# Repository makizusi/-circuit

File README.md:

https://github.com/makizusi/-circuit/blob/main/%E8%A8%AD%E8%A8%88%E6%84%8F%E5%9B%B3.pdf

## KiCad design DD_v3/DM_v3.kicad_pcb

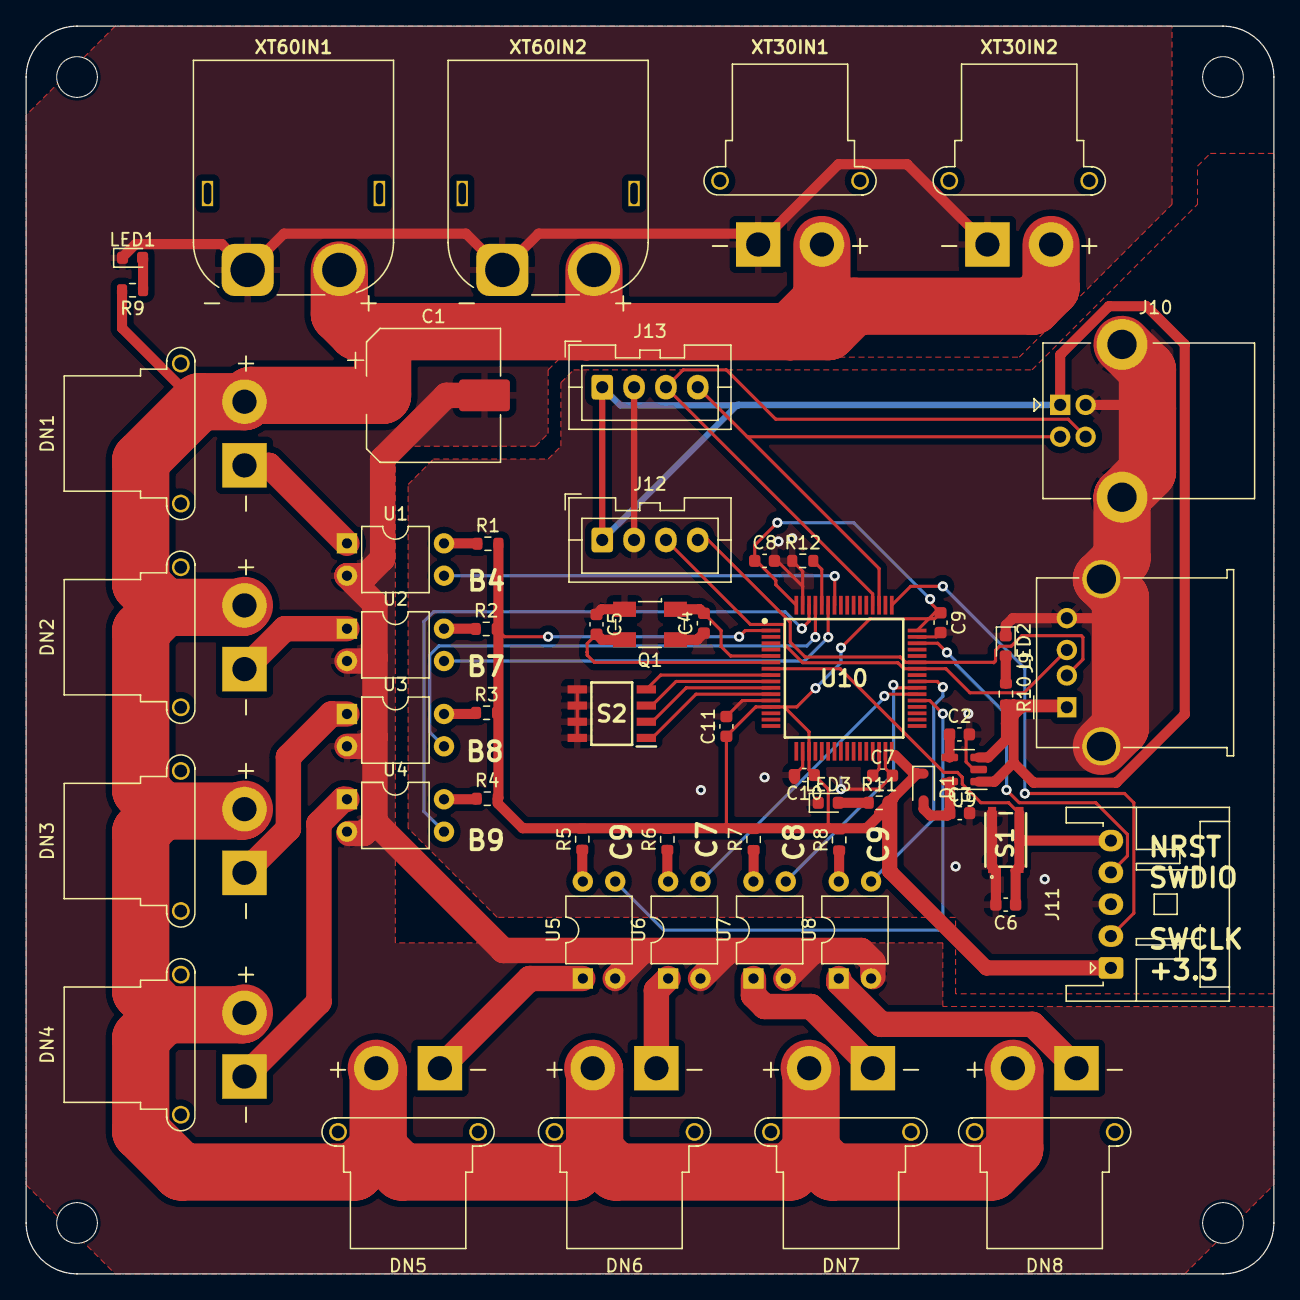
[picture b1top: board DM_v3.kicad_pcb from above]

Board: 2 copper layers, 98.0 x 98.0 mm, 57 parts (0 on the bottom side), 49 nets.

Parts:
C1: 330μf; CP_Elec_10x10
C2: 4.7nF; C_0603_1608Metric
C3: 2.2uF; C_0603_1608Metric
C4, C5: 22pF; C_0603_1608Metric
C6, C8, C9, C10, C11: 0.1uF; C_0603_1608Metric
C7: 4.7uF; C_0603_1608Metric
D1: BAT60JFILM; D_SOD-323
DN1, DN2, DN3, DN4, DN5, DN6, DN7, DN8: Conn_01x02; AMASS_XT30PW-F_1x02_P2.50mm_Horizontal
J9: USB_A; USB_A_Molex_67643_Horizontal
J10: USB_B; USB_B_Lumberg_2411_02_Horizontal
J11: stlink; JST_XA_S05B-XASK-1_1x05_P2.50mm_Horizontal
J12, J13: Conn_01x04; JST_XA_B04B-XASK-1_1x04_P2.50mm_Vertical
LED1: vcc; LED_0603_1608Metric
LED2: 5v; LED_0603_1608Metric
LED3: 3.3v; LED_0603_1608Metric
Q1: ABM3B-8.000MHZ-B2-T; Crystal_SMD_Abracon_ABM3B-4Pin_5.0x3.2mm
R1, R2, R3, R4, R5, R6, R7, R8: 100; R_0603_1608Metric
R9, R10: 4.7k; R_0603_1608Metric
R11: 1k; R_0603_1608Metric
R12: 10k; R_0603_1608Metric
S1: SKRPACE010; SMT_4.2X3.2_
S2: KHS42E; NE555DR
U1, U2, U3, U4, U5, U6, U7, U8: TLP627; DIP-4_W7.62mm
U9: SPX3819M5-L; SOT-23-5
U10: STM32F446RCT7; QFP50P1200X1200X160-64N
XT30IN1, XT30IN2: Conn_01x02; AMASS_XT30PW-F_1x02_P2.50mm_Horizontal
XT60IN1, XT60IN2: power; AMASS_XT60PW-M_1x02_P7.20mm_Horizontal

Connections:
+3.3V: C8.1, C9.1, C10.1, C11.1, D1.1, J11.1, R1.2, R2.2, R3.2, R4.2, R5.2, R6.2, R7.2, R8.2, R11.2, U10.1 (VBAT), U10.13 (VDDA/VREF+), U10.19 (VDD_4), U10.32 (VDD_1), U10.48 (VDD_2), U10.64 (VDD_3)
+5V: J9.1 (VBUS), J10.1 (VBUS), J12.1, J13.1, R10.2, U9.1 (IN), U9.3 (EN)
A9: J9.3 (D+), J12.3, U10.42 (PA9)
A10: J9.2 (D-), J12.4, U10.43 (PA10)
B6: U1.3, U10.58 (PB6)
B7: U2.3, U10.59 (PB7)
B8: U3.3, U10.61 (PB8)
B9: U4.3, U10.62 (PB9)
C6: U5.3, U10.37 (PC6)
C7: U6.3, U10.38 (PC7)
C8: U7.3, U10.39 (PC8)
C9: U8.3, U10.40 (PC9)
C10: J10.2 (D-), J13.4, U10.51 (PC10)
C11: J10.3 (D+), J13.3, U10.52 (PC11)
GND: C2.2, C3.2, C4.1, C5.1, C6.2, C7.2, C8.2, C9.2, C10.2, C11.2, J9.4 (GND), J9.5 (Shield), J10.4 (GND), J10.5 (Shield), J11.3, J12.2, J13.2, LED2.1 (K), LED3.1 (K), Q1.2 (GND), Q1.4 (GND), R12.1, S1.1, S1.2, S2.5, S2.6, S2.7, S2.8, U9.2 (GND), U10.12 (VSSA/VREF-), U10.18 (VSS_4), U10.31 (VSS_1), U10.47 (VSS_2), U10.63 (VSS_3)
GNDPWR: C1.2, LED1.1 (K), U1.2, U2.2, U3.2, U4.2, U5.2, U6.2, U7.2, U8.2, XT30IN1.1, XT30IN2.1, XT60IN1.1, XT60IN2.1
unnamed: DN1.1, U1.1
unnamed: DN2.1, U2.1
unnamed: DN3.1, U3.1
unnamed: DN4.1, U4.1
unnamed: DN5.1, U5.1
unnamed: DN6.1, U6.1
unnamed: DN7.1, U7.1
unnamed: DN8.1, U8.1
unnamed: LED1.2 (A), R9.1
unnamed: LED2.2 (A), R10.1
unnamed: LED3.2 (A), R11.1
unnamed: R1.1, U1.4
unnamed: R2.1, U2.4
unnamed: R3.1, U3.4
unnamed: R4.1, U4.4
unnamed: R5.1, U5.4
unnamed: R6.1, U6.4
unnamed: R7.1, U7.4
unnamed: R8.1, U8.4
unnamed: C2.1, U9.4 (ADJ)
unnamed: C3.1, D1.2, U9.5 (OUT)
unnamed: R12.2, U10.60 (BOOT0)
unnamed: S2.4, U10.8 (PC0)
unnamed: S2.3, U10.9 (PC1)
unnamed: S2.2, U10.10 (PC2)
unnamed: S2.1, U10.11 (PC3)
unnamed: C4.2, Q1.1, U10.5 (PH0-OSC_IN)
unnamed: C5.2, Q1.3, U10.6 (PH1-OSC_OUT)
unnamed: C7.1, U10.30 (VCAP_1)
VCC: C1.1, DN1.2, DN2.2, DN3.2, DN4.2, DN5.2, DN6.2, DN7.2, DN8.2, R9.2, XT30IN1.2, XT30IN2.2, XT60IN1.2, XT60IN2.2
nrst: C6.1, J11.5, S1.3, S1.4, U10.7 (NRST)
swclk: J11.2, U10.49 (PA14)
swdio: J11.4, U10.46 (PA13)

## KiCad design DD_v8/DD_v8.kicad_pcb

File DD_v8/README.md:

# ALTAIR_SERVO_MODULE_V6
ALTAIR_SERVO_MODULE_V6

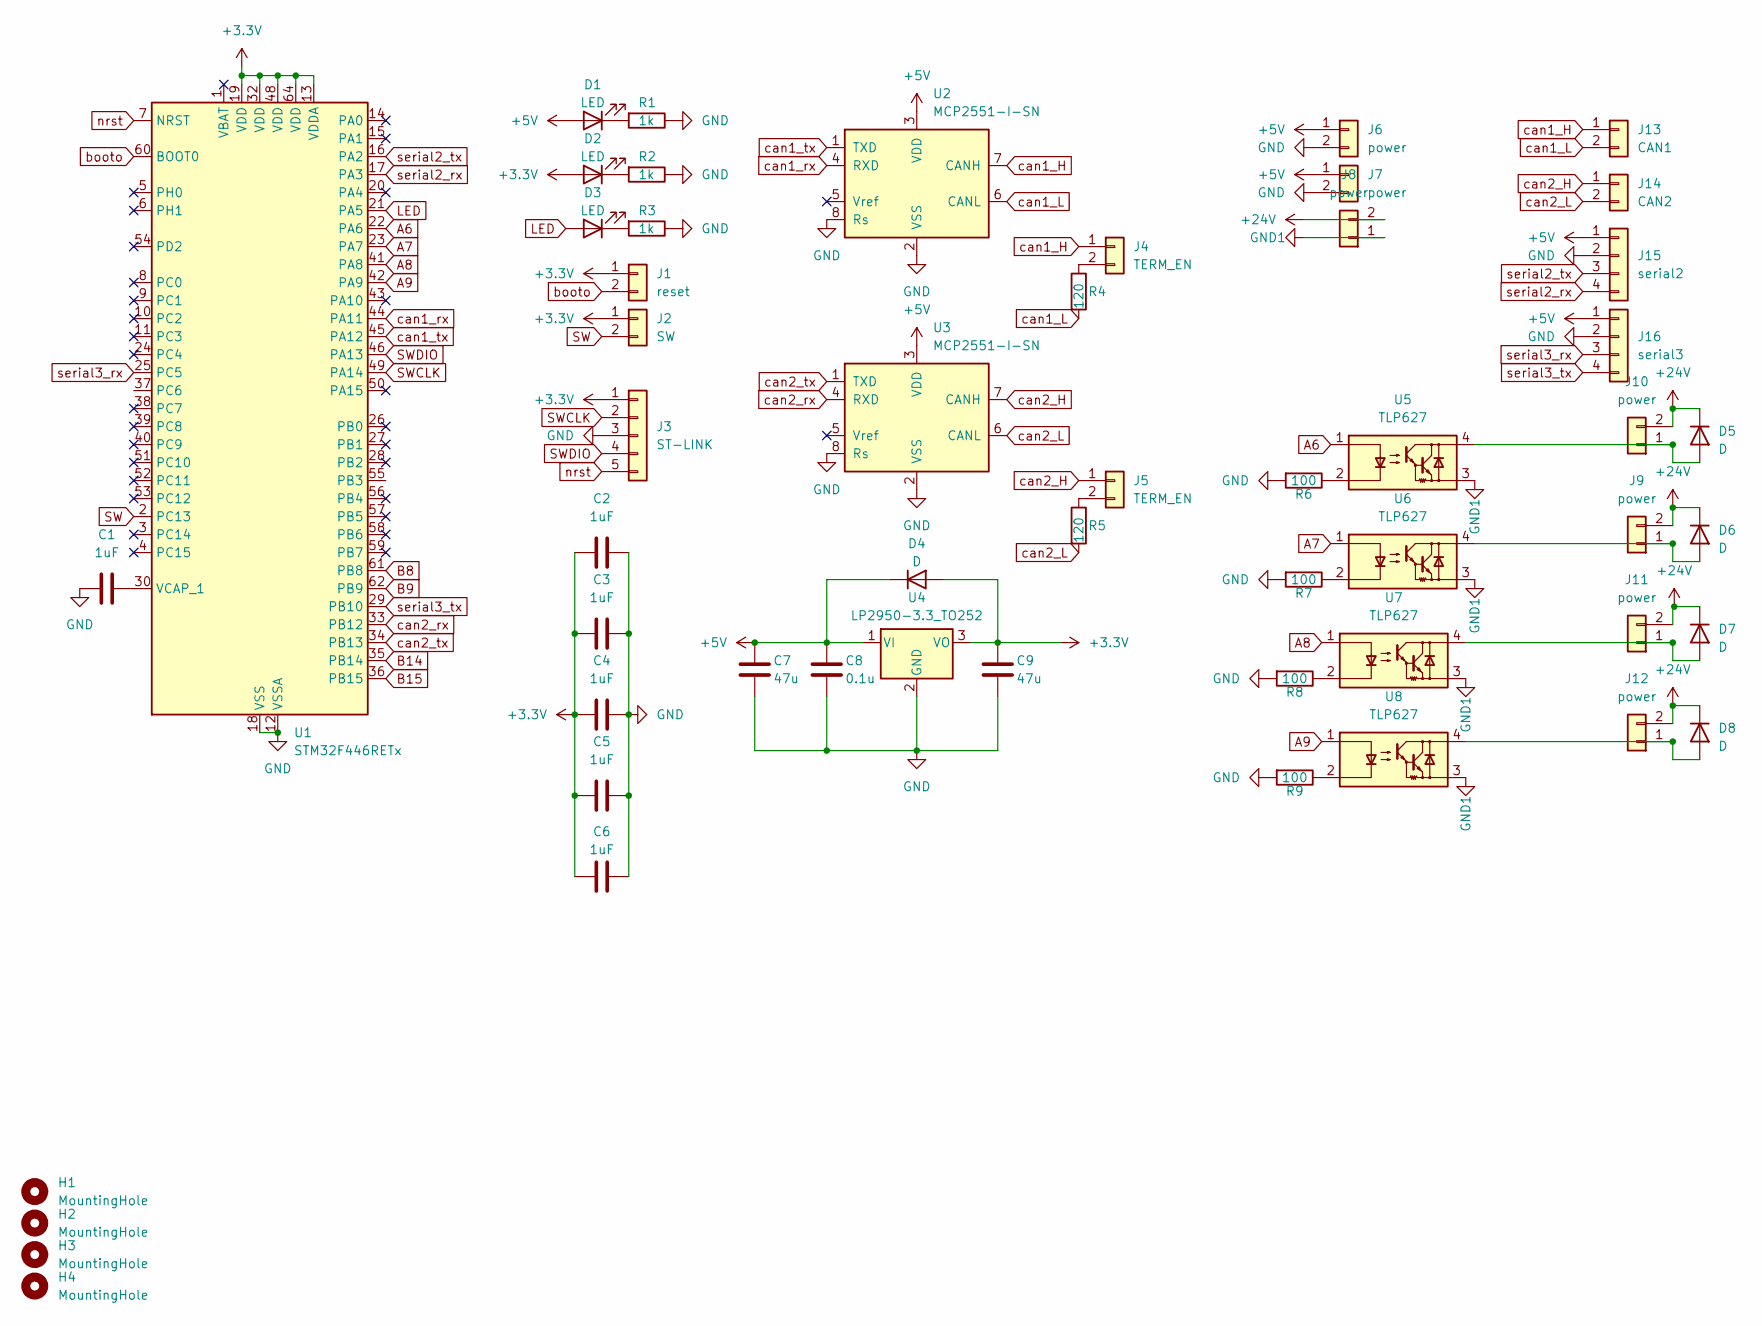
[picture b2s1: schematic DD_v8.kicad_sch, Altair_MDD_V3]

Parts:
C1, C2, C3, C4, C5, C6: 1uF; C_0603_1608Metric
C7, C9: 47u; C_0603_1608Metric
C8: 0.1u; C_0603_1608Metric
D1, D2, D3: LED; LED_0603_1608Metric
D4: D; D_0603_1608Metric
D5, D6, D7, D8: D; D_SOD-128
H1, H2, H3, H4: MountingHole; MountingHole_3.2mm_M3_Pad_Via
J1: reset; PinSocket_1x02_P2.54mm_Vertical
J2: SW; PinSocket_1x02_P2.54mm_Vertical
J3: ST-LINK; PinSocket_1x05_P2.54mm_Vertical
J4, J5: TERM_EN; PinSocket_1x02_P2.54mm_Vertical
J6, J7: power; JST_XA_S02B-XASK-1_1x02_P2.50mm_Horizontal
J8, J9, J10, J11, J12: power; AMASS_XT30PW-M_1x02_P2.50mm_Horizontal
J13: CAN1; JST_XA_S02B-XASK-1_1x02_P2.50mm_Horizontal
J14: CAN2; JST_XA_S02B-XASK-1_1x02_P2.50mm_Horizontal
J15: serial2; JST_XA_B04B-XASK-1-A_1x04_P2.50mm_Vertical
J16: serial3; JST_XA_B04B-XASK-1-A_1x04_P2.50mm_Vertical
R1, R2, R3: 1k; R_0603_1608Metric
R4, R5: 120; R_0603_1608Metric
R6, R7, R8, R9: 100; R_0603_1608Metric
U1: STM32F446RETx; LQFP-64_10x10mm_P0.5mm
U2, U3: MCP2551-I-SN; SOIC-8_3.9x4.9mm_P1.27mm
U4: LP2950-3.3_TO252; TO-252-2
U5, U6, U7, U8: TLP627; DIP-4_W7.62mm_SMDSocket_SmallPads

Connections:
+3.3V: C2.1, C3.1, C4.1, C5.1, C6.1, C9.1, D2.2 (A), D4.2 (A), J1.1, J2.1, J3.1, U1.13 (VDDA), U1.19 (VDD), U1.32 (VDD), U1.48 (VDD), U1.64 (VDD), U4.3 (VO)
+5V: C7.1, C8.1, D1.2 (A), D4.1 (K), J6.1, J7.1, J15.1, J16.1, U2.3 (VDD), U3.3 (VDD), U4.1 (VI)
+24V: D5.1 (K), D6.1 (K), D7.1 (K), D8.1 (K), J8.2, J9.2, J10.2, J11.2, J12.2
A6: U1.22 (PA6), U5.1
A7: U1.23 (PA7), U6.1
A8: U1.41 (PA8), U7.1
A9: U1.42 (PA9), U8.1
B8: U1.61 (PB8)
B9: U1.62 (PB9)
B14: U1.35 (PB14)
B15: U1.36 (PB15)
GND: C1.1, C2.2, C3.2, C4.2, C5.2, C6.2, C7.2, C8.2, C9.2, J3.3, J6.2, J7.2, J15.2, J16.2, R1.1, R2.1, R3.1, R6.2, R7.2, R8.2, R9.2, U1.12 (VSSA), U1.18 (VSS), U1.31 (VSS), U1.47 (VSS), U1.63 (VSS), U2.2 (VSS), U2.8 (Rs), U3.2 (VSS), U3.8 (Rs), U4.2 (GND)
GND1: J8.1, U5.3, U6.3, U7.3, U8.3
LED: D3.2 (A), U1.21 (PA5)
unnamed: D1.1 (K), R1.2
unnamed: D2.1 (K), R2.2
unnamed: D3.1 (K), R3.2
unnamed: D5.2 (A), J10.1, U5.4
unnamed: D6.2 (A), J9.1, U6.4
unnamed: D7.2 (A), J11.1, U7.4
unnamed: D8.2 (A), J12.1, U8.4
unnamed: J4.2, R4.1
unnamed: J5.2, R5.1
unnamed: R6.1, U5.2
unnamed: R7.1, U6.2
unnamed: R8.1, U7.2
unnamed: R9.1, U8.2
unnamed: C1.2, U1.30 (VCAP_1)
SW: J2.2, U1.2 (PC13)
SWCLK: J3.2, U1.49 (PA14)
SWDIO: J3.4, U1.46 (PA13)
booto: J1.2, U1.60 (BOOT0)
can1_H: J4.1, J13.1, U2.7 (CANH)
can1_L: J13.2, R4.2, U2.6 (CANL)
can1_rx: U1.44 (PA11), U2.4 (RXD)
can1_tx: U1.45 (PA12), U2.1 (TXD)
can2_H: J5.1, J14.1, U3.7 (CANH)
can2_L: J14.2, R5.2, U3.6 (CANL)
can2_rx: U1.33 (PB12), U3.4 (RXD)
can2_tx: U1.34 (PB13), U3.1 (TXD)
nrst: J3.5, U1.7 (NRST)
serial2_rx: J15.4, U1.17 (PA3)
serial2_tx: J15.3, U1.16 (PA2)
serial3_rx: J16.3, U1.25 (PC5)
serial3_tx: J16.4, U1.29 (PB10)

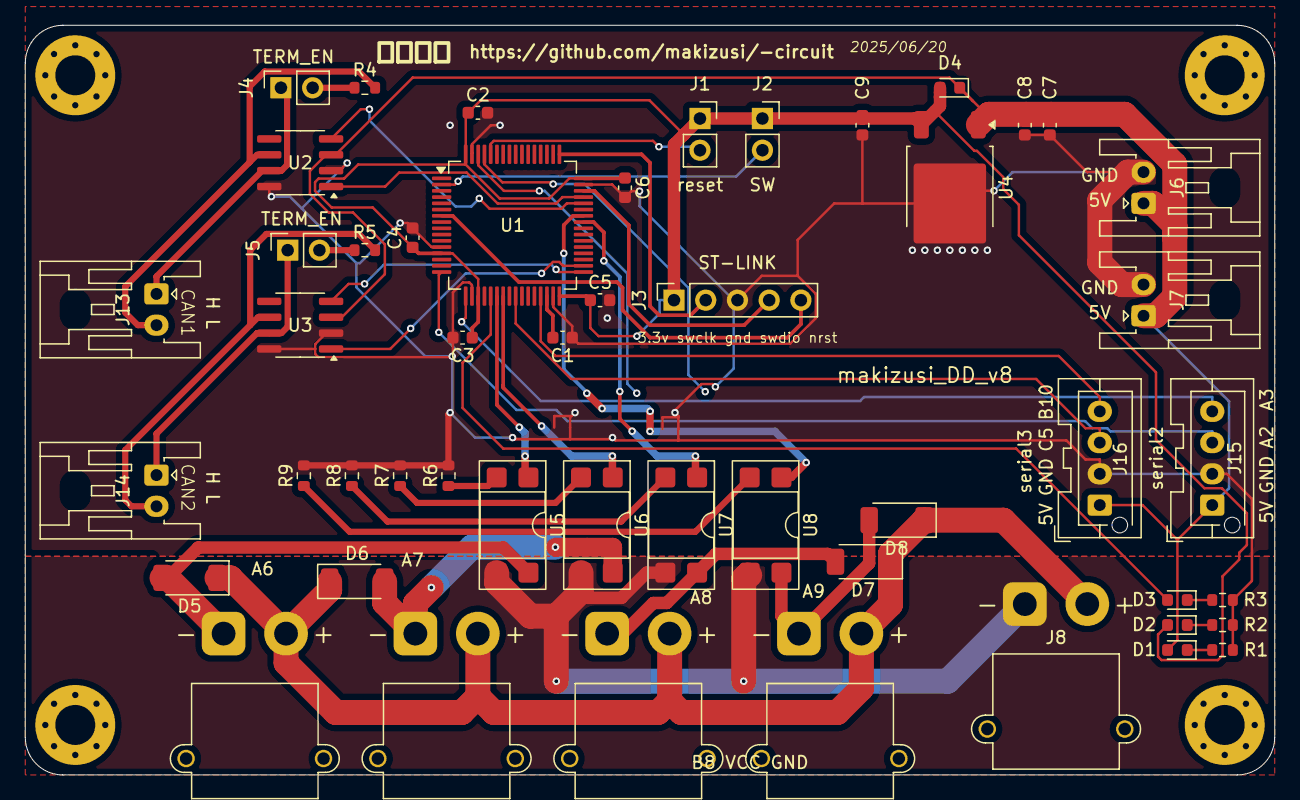
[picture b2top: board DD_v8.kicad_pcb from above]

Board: 2 copper layers, 100.0 x 60.0 mm, 54 parts (0 on the bottom side), 41 nets.

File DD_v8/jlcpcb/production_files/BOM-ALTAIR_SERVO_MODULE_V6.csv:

Comment,Designator,Footprint,LCSC,Quantity
0.1u,"C10,C12,C13,C8",C_0603_1608Metric,C125205,4
LP2950-3.3_TO252,U4,TO-252-2,C129994,1
47u,"C7,C9",C_0603_1608Metric,C140782,2
120,"R4,R5",R_0603_1608Metric,C14709,2
1uF,"C1,C2,C3,C4,C5,C6",C_0603_1608Metric,C1592,6
LED,"D1,D2,D3",LED_0603_1608Metric,C2290,3
TLP2105_F_,"IC1,IC2,IC3",TLP2105,C2880451,3
D,D4,D_0603_1608Metric,C3758192,1
STM32F446RETx,U1,LQFP-64_10x10mm_P0.5mm,C69336,1
MCP2551-I-SN,"U2,U3",SOIC-8_3.9x4.9mm_P1.27mm,C7376,2
1k,"R1,R2,R3",R_0603_1608Metric,C78748,3
Motor_Servo,M1,JST_XA_S03B-XASK-1_1x03_P2.50mm_Horizontal,,1
SW,J2,PinSocket_1x02_P2.54mm_Vertical,,1
power,J6,JST_XA_S02B-XASK-1_1x02_P2.50mm_Horizontal,,1
MountingHole,H2,MountingHole_3.2mm_M3_Pad_Via,,1
serial2,J15,JST_XA_B04B-XASK-1-A_1x04_P2.50mm_Vertical,,1
Motor_Servo,M5,JST_XA_S03B-XASK-1_1x03_P2.50mm_Horizontal,,1
TERM_EN,J4,PinSocket_1x02_P2.54mm_Vertical,,1
power,J8,AMASS_XT30PW-M_1x02_P2.50mm_Horizontal,,1
Motor_Servo,M2,JST_XA_S03B-XASK-1_1x03_P2.50mm_Horizontal,,1
serial3,J16,JST_XA_B04B-XASK-1-A_1x04_P2.50mm_Vertical,,1
reset,J1,PinSocket_1x02_P2.54mm_Vertical,,1
MountingHole,H1,MountingHole_3.2mm_M3_Pad_Via,,1
TERM_EN,J5,PinSocket_1x02_P2.54mm_Vertical,,1
Motor_Servo,M4,JST_XA_S03B-XASK-1_1x03_P2.50mm_Horizontal,,1
MountingHole,H4,MountingHole_3.2mm_M3_Pad_Via,,1
CAN2,J14,JST_XA_S02B-XASK-1_1x02_P2.50mm_Horizontal,,1
Motor_Servo,M3,JST_XA_S03B-XASK-1_1x03_P2.50mm_Horizontal,,1
ST-LINK,J3,PinSocket_1x05_P2.54mm_Vertical,,1
CAN1,J13,JST_XA_S02B-XASK-1_1x02_P2.50mm_Horizontal,,1
Motor_Servo,M6,JST_XA_S03B-XASK-1_1x03_P2.50mm_Horizontal,,1
power,J7,JST_XA_S02B-XASK-1_1x02_P2.50mm_Horizontal,,1
MountingHole,H3,MountingHole_3.2mm_M3_Pad_Via,,1

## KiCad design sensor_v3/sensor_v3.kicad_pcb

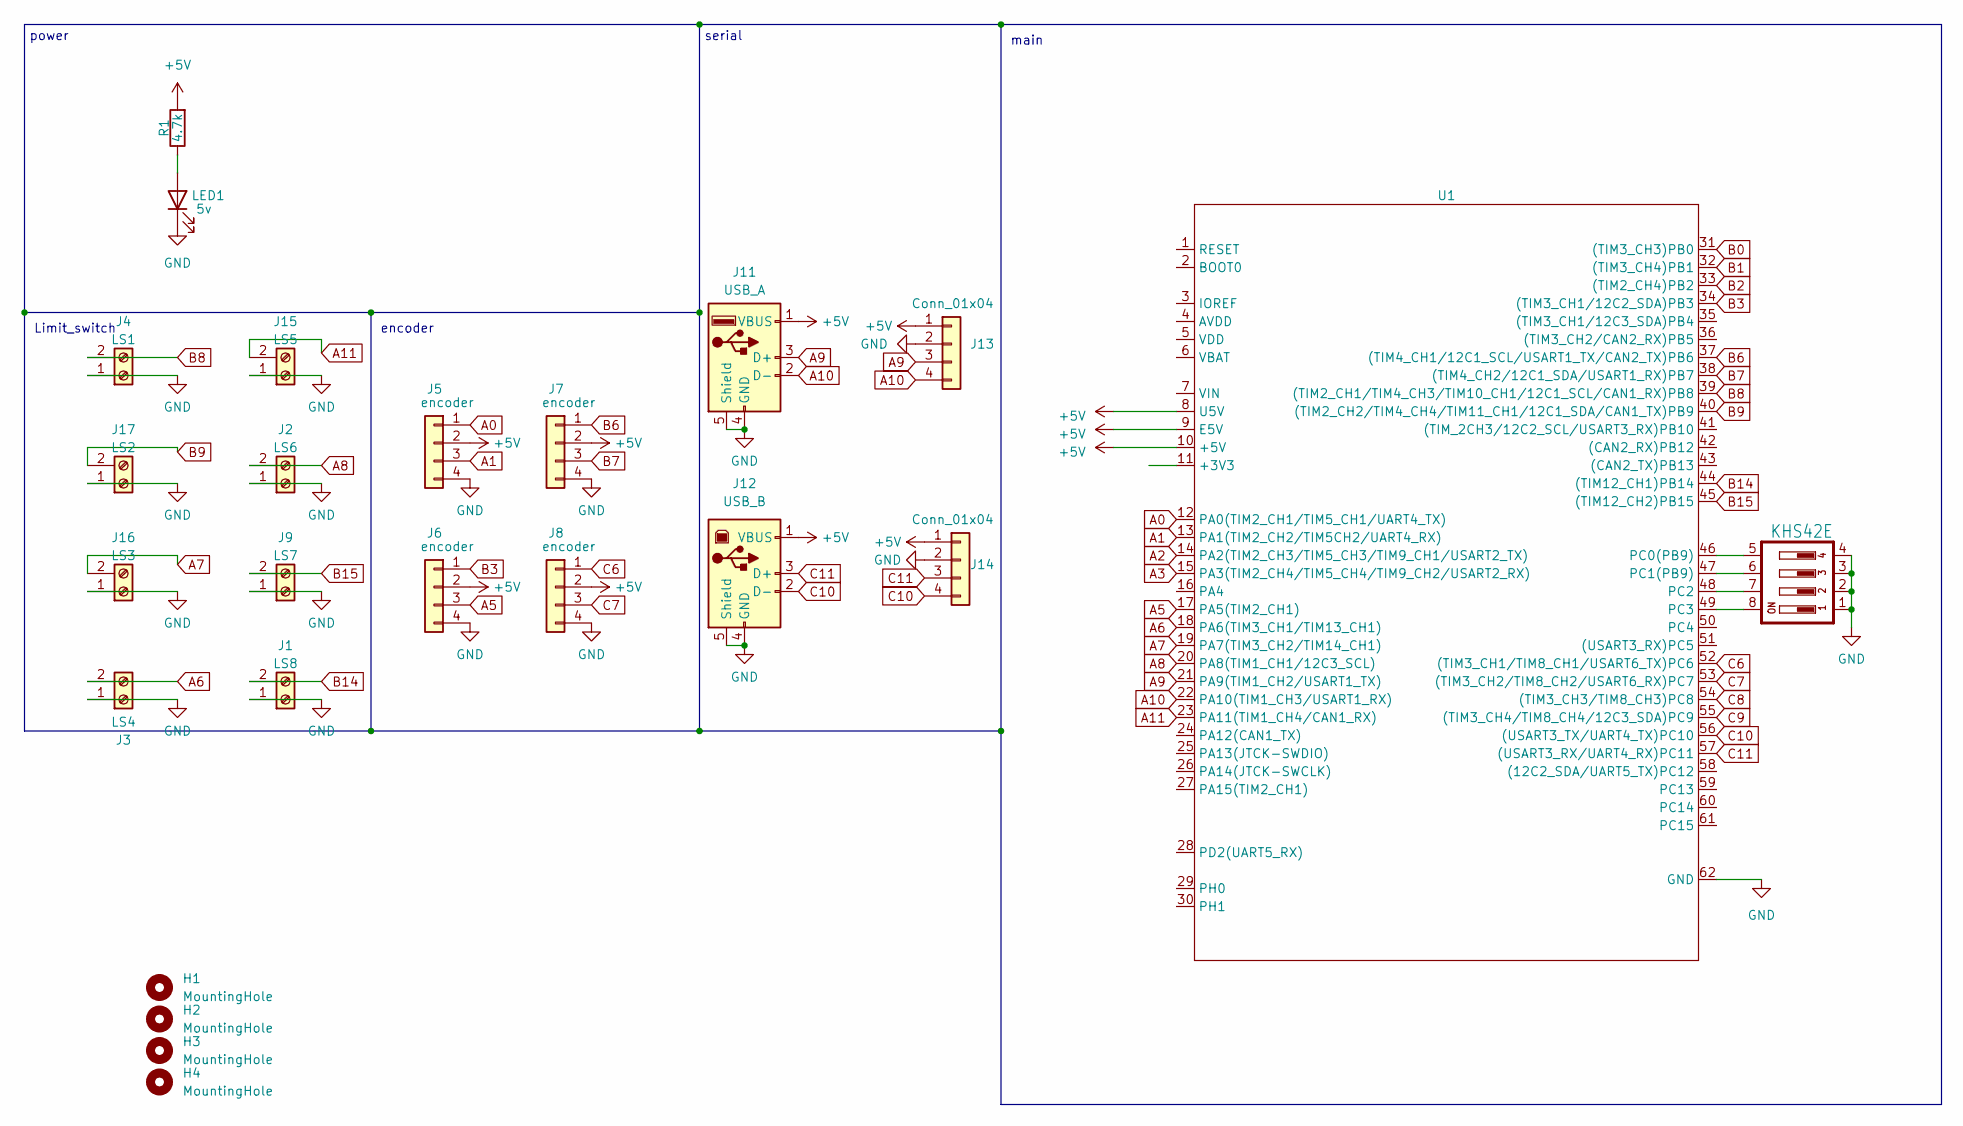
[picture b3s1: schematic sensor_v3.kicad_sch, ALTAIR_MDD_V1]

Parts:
H1, H2, H3, H4: MountingHole; MountingHole_3.2mm_M3
J1: LS8; JST_XA_S02B-XASK-1_1x02_P2.50mm_Horizontal
J2: LS6; JST_XA_S02B-XASK-1_1x02_P2.50mm_Horizontal
J3: LS4; JST_XA_S02B-XASK-1_1x02_P2.50mm_Horizontal
J4: LS1; JST_XA_S02B-XASK-1_1x02_P2.50mm_Horizontal
J5, J6, J7, J8: encoder; JST_XA_S04B-XASK-1_1x04_P2.50mm_Horizontal
J9: LS7; JST_XA_S02B-XASK-1_1x02_P2.50mm_Horizontal
J11: USB_A; USB_A_Molex_67643_Horizontal
J12: USB_B; USB_B_Lumberg_2411_02_Horizontal
J13, J14: Conn_01x04; JST_XA_B04B-XASK-1_1x04_P2.50mm_Vertical
J15: LS5; JST_XA_S02B-XASK-1_1x02_P2.50mm_Horizontal
J16: LS3; JST_XA_S02B-XASK-1_1x02_P2.50mm_Horizontal
J17: LS2; JST_XA_S02B-XASK-1_1x02_P2.50mm_Horizontal
LED1: 5v; LED_0603_1608Metric
R1: 4.7k; R_0603_1608Metric
S2: KHS42E; NE555DR
U1: STM32F446RE_Nucleo

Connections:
+5V: J5.2, J6.2, J7.2, J8.2, J11.1 (VBUS), J12.1 (VBUS), J13.1, J14.1, R1.2, U1.8 (U5V), U1.9 (E5V), U1.10 (+5V)
A0: J5.1, U1.12 (PA0(TIM2_CH1/TIM5_CH1/UART4_TX))
A1: J5.3, U1.13 (PA1(TIM2_CH2/TIM5CH2/UART4_RX))
A2: U1.14 (PA2(TIM2_CH3/TIM5_CH3/TIM9_CH1/USART2_T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)
A3: U1.15 (PA3(TIM2_CH4/TIM5_CH4/TIM9_CH2/USART2_R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)
A5: J6.3, U1.17 (PA5(TIM2_CH1))
A6: J3.2, U1.18 (PA6(TIM3_CH1/TIM13_CH1))
A7: J16.2, U1.19 (PA7(TIM3_CH2/TIM14_CH1))
A8: J2.2, U1.20 (PA8(TIM1_CH1/12C3_SCL))
A9: J11.3 (D+), J13.3, U1.21 (PA9(TIM1_CH2/USART1_TX))
A10: J11.2 (D-), J13.4, U1.22 (PA10(TIM1_CH3/USART1_RX))
A11: J15.2, U1.23 (PA11(TIM1_CH4/CAN1_RX))
B0: U1.31 ((TIM3_CH3)PB0)
B1: U1.32 ((TIM3_CH4)PB1)
B2: U1.33 ((TIM2_CH4)PB2)
B3: J6.1, U1.34 ((TIM3_CH1/12C2_SDA)PB3)
B6: J7.1, U1.37 ((TIM4_CH1/12C1_SCL/USART1_TX/CAN2_TX)PB6)
B7: J7.3, U1.38 ((TIM4_CH2/12C1_SDA/USART1_RX)PB7)
B8: J4.2, U1.39 ((TIM2_CH1/TIM4_CH3/TIM10_CH1/12C1_SCL/C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)
B9: J17.2, U1.40 ((TIM2_CH2/TIM4_CH4/TIM11_CH1/12C1_SDA/C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)
B14: J1.2, U1.44 ((TIM12_CH1)PB14)
B15: J9.2, U1.45 ((TIM12_CH2)PB15)
C6: J8.1, U1.52 ((TIM3_CH1/TIM8_CH1/USART6_TX)PC6)
C7: J8.3, U1.53 ((TIM3_CH2/TIM8_CH2/USART6_RX)PC7)
C8: U1.54 ((TIM3_CH3/TIM8_CH3)PC8)
C9: U1.55 ((TIM3_CH4/TIM8_CH4/12C3_SDA)PC9)
C10: J12.2 (D-), J14.4, U1.56 ((USART3_TX/UART4_TX)PC10)
C11: J12.3 (D+), J14.3, U1.57 ((USART3_RX/UART4_RX)PC11)
GND: J1.1, J2.1, J3.1, J4.1, J5.4, J6.4, J7.4, J8.4, J9.1, J11.4 (GND), J11.5 (Shield), J12.4 (GND), J12.5 (Shield), J13.2, J14.2, J15.1, J16.1, J17.1, LED1.1 (K), S2.1, S2.2, S2.3, S2.4, U1.62 (GND)
unnamed: LED1.2 (A), R1.1
unnamed: S2.5, U1.46 (PC0(PB9))
unnamed: S2.6, U1.47 (PC1(PB9))
unnamed: S2.7, U1.48 (PC2)
unnamed: S2.8, U1.49 (PC3)

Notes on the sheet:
serial
encoder
main
power
Limit_switch

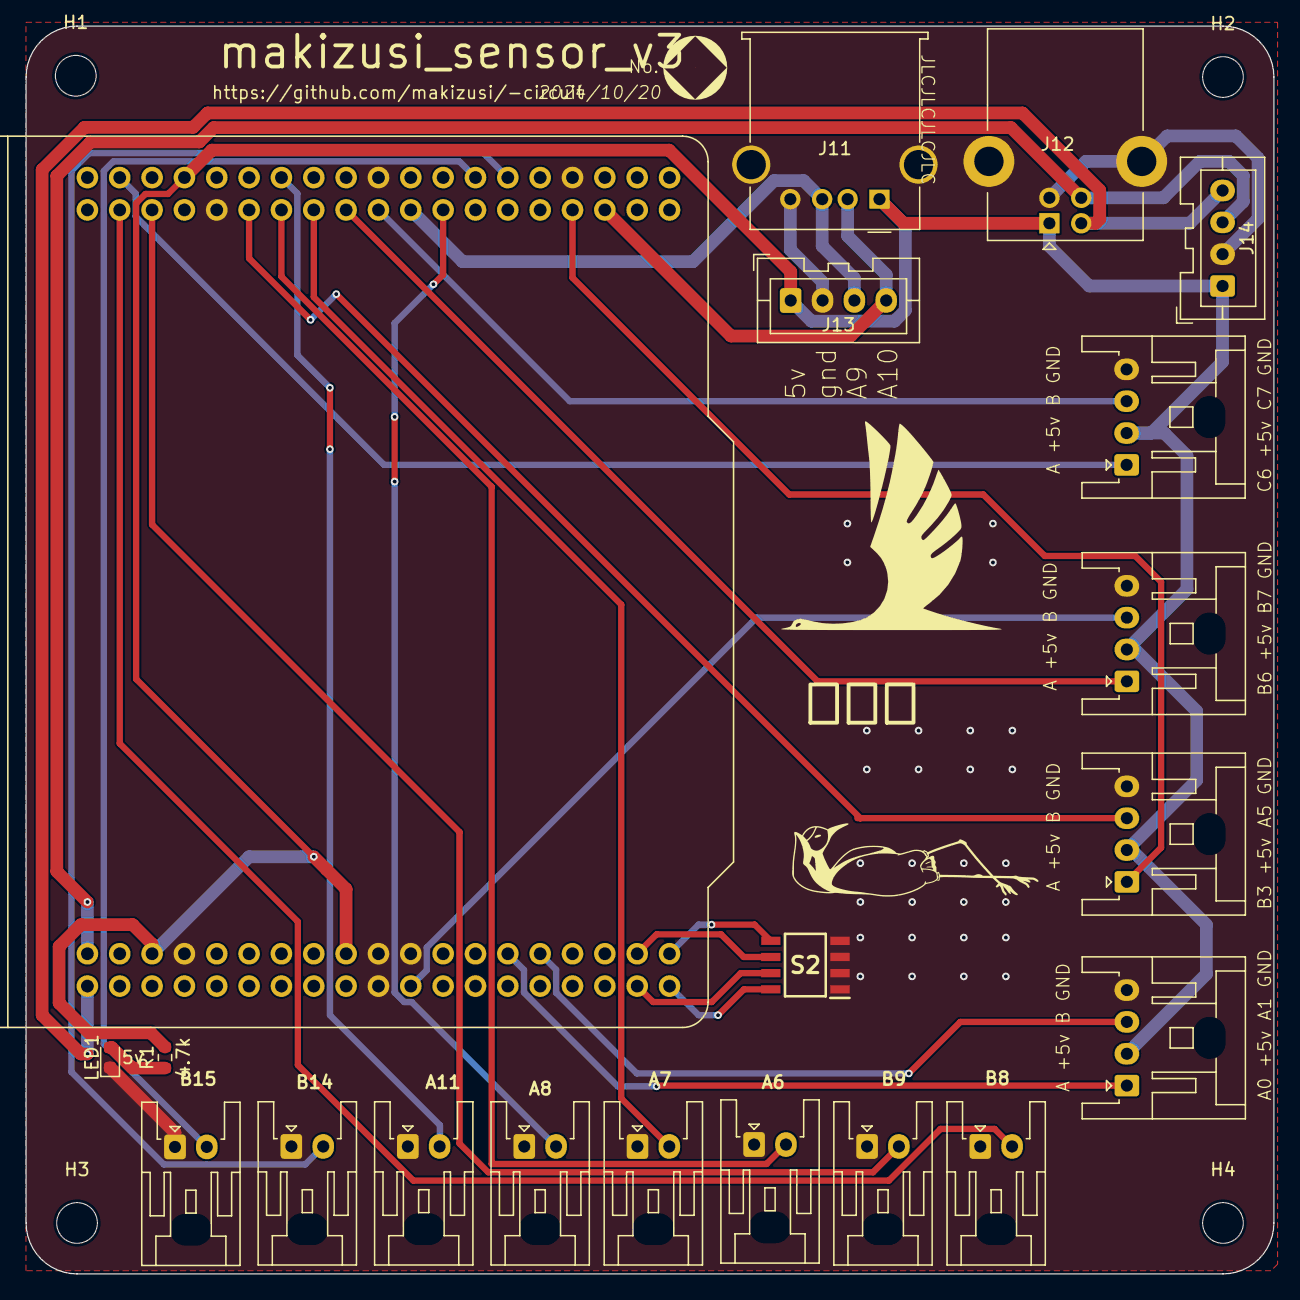
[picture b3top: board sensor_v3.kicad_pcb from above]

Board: 2 copper layers, 98.0 x 98.0 mm, 24 parts (0 on the bottom side), 27 nets.

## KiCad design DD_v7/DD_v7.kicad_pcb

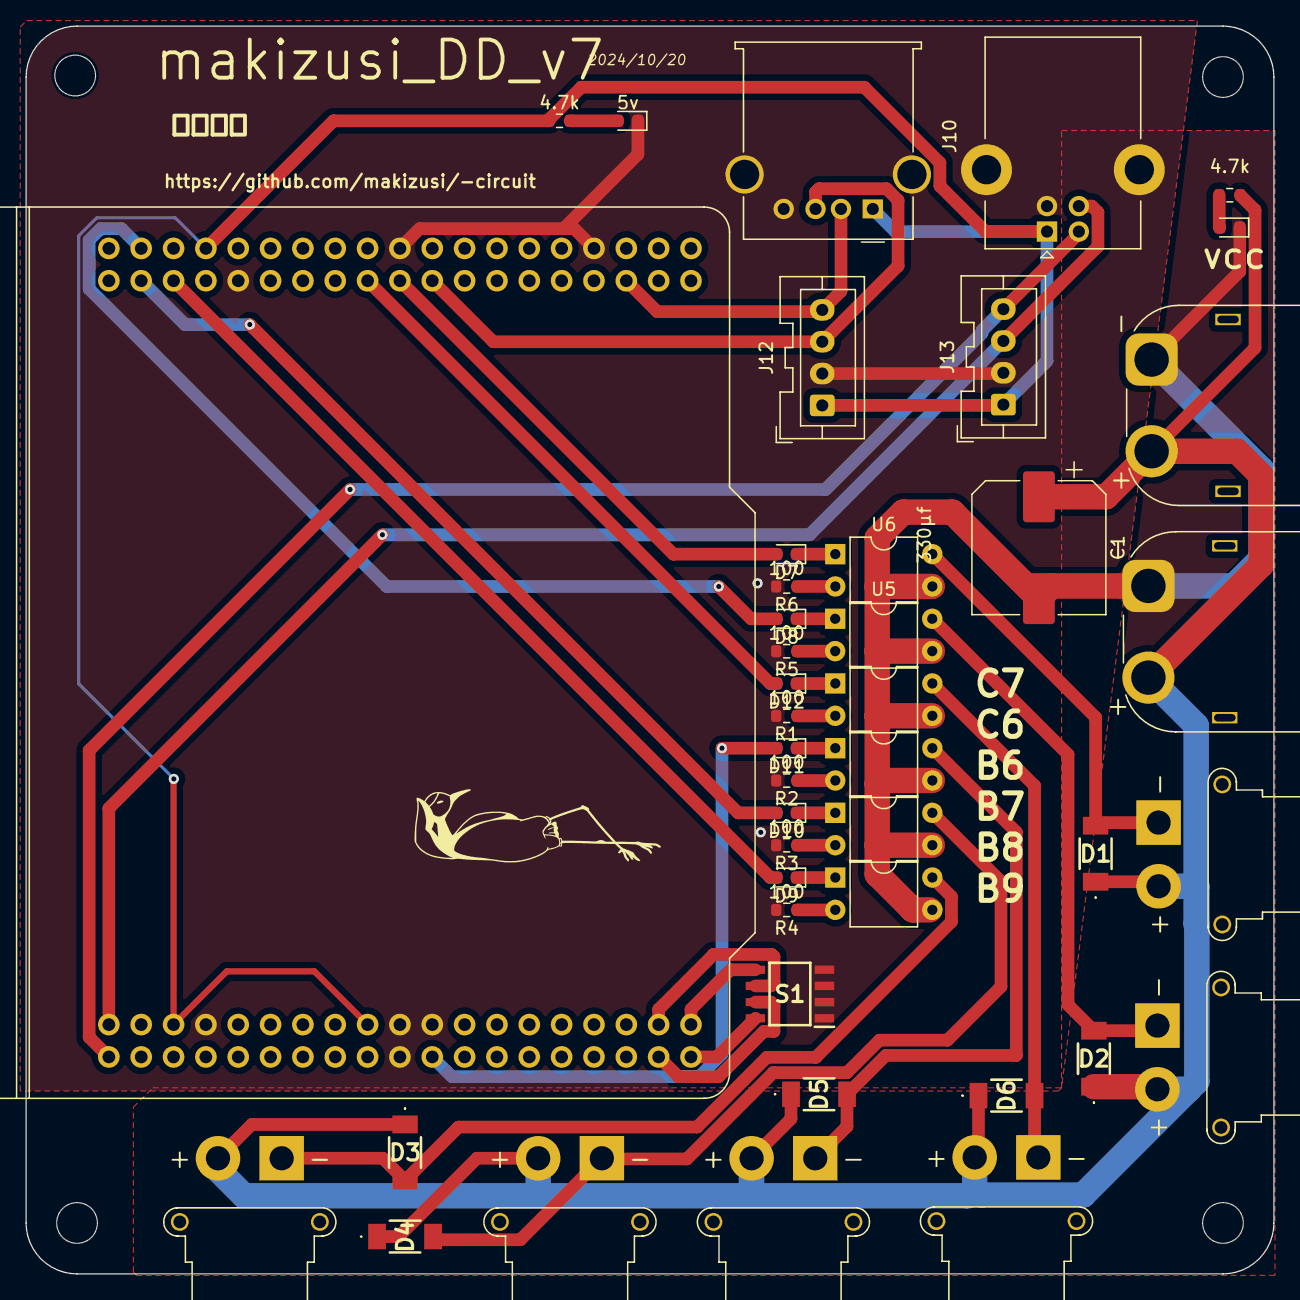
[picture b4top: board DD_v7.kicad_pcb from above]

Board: 2 copper layers, 98.0 x 98.0 mm, 47 parts (0 on the bottom side), 38 nets.

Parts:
C1: 330μf; CP_Elec_10x10
D1, D2, D3, D4, D5, D6: D; RF201LAM2STR
D7, D8, D9, D10, D11, D12: LED; LED_0603_1608Metric
H1, H2, H3, H4: MountingHole; MountingHole_3.2mm_M3
J1, J2, J3, J4, J5, J6: Conn_01x02; AMASS_XT30PW-F_1x02_P2.50mm_Horizontal
J9: USB_A; USB_A_Molex_67643_Horizontal
J10: USB_B; USB_B_Lumberg_2411_02_Horizontal
J12, J13: Conn_01x04; JST_XA_B04B-XASK-1_1x04_P2.50mm_Vertical
LED1: vcc; LED_0603_1608Metric
LED2: 5v; LED_0603_1608Metric
R1, R2, R3, R4, R5, R6: 100; R_0603_1608Metric
R9, R10: 4.7k; R_0603_1608Metric
S1: KHS42E; NE555DR
U1, U2, U3, U4, U5, U6: TLP627; DIP-4_W7.62mm
U10: STM32F446RE_Nucleo
XT60IN1, XT60OUT1: power; AMASS_XT60PW-M_1x02_P7.20mm_Horizontal

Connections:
+5V: J9.1 (VBUS), J10.1 (VBUS), J12.1, J13.1, R10.2, U10.8 (U5V), U10.9 (E5V), U10.10 (+5V)
A9: J9.3 (D+), J12.3, U10.21 (PA9(TIM1_CH2/USART1_TX))
A10: J9.2 (D-), J12.4, U10.22 (PA10(TIM1_CH3/USART1_RX))
B6: D12.2 (A), U10.37 ((TIM4_CH1/12C1_SCL/USART1_TX/CAN2_TX)PB6)
B7: D11.2 (A), U10.38 ((TIM4_CH2/12C1_SDA/USART1_RX)PB7)
B8: D10.2 (A), U10.39 ((TIM2_CH1/TIM4_CH3/TIM10_CH1/12C1_SCL/C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)
B9: D9.2 (A), U10.40 ((TIM2_CH2/TIM4_CH4/TIM11_CH1/12C1_SDA/C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)
C6: D8.2 (A), U10.52 ((TIM3_CH1/TIM8_CH1/USART6_TX)PC6)
C7: D7.2 (A), U10.53 ((TIM3_CH2/TIM8_CH2/USART6_RX)PC7)
C10: J10.2 (D-), J13.4, U10.56 ((USART3_TX/UART4_TX)PC10)
C11: J10.3 (D+), J13.3, U10.57 ((USART3_RX/UART4_RX)PC11)
GND: J9.4 (GND), J9.5 (Shield), J10.4 (GND), J10.5 (Shield), J12.2, J13.2, LED2.1 (K), R1.2, R2.2, R3.2, R4.2, R5.2, R6.2, S1.1, S1.2, S1.3, S1.4, U10.62 (GND)
GNDPWR: C1.2, LED1.1 (K), U1.3, U2.3, U3.3, U4.3, U5.3, U6.3, XT60IN1.1, XT60OUT1.1
unnamed: D1.2 (A), J6.1, U6.4
unnamed: D2.2 (A), J5.1, U5.4
unnamed: D3.2 (A), J4.1, U4.4
unnamed: D4.2 (A), J3.1, U3.4
unnamed: D5.2 (A), J2.1, U2.4
unnamed: D6.2 (A), J1.1, U1.4
unnamed: D7.1 (K), U6.1
unnamed: D8.1 (K), U5.1
unnamed: D9.1 (K), U4.1
unnamed: D10.1 (K), U3.1
unnamed: D11.1 (K), U2.1
unnamed: D12.1 (K), U1.1
unnamed: LED1.2 (A), R9.1
unnamed: LED2.2 (A), R10.1
unnamed: R1.1, U1.2
unnamed: R2.1, U2.2
unnamed: R3.1, U3.2
unnamed: R4.1, U4.2
unnamed: R5.1, U5.2
unnamed: R6.1, U6.2
unnamed: S1.5, U10.46 (PC0(PB9))
unnamed: S1.6, U10.47 (PC1(PB9))
unnamed: S1.7, U10.48 (PC2)
unnamed: S1.8, U10.49 (PC3)
VCC: C1.1, D1.1 (K), D2.1 (K), D3.1 (K), D4.1 (K), D5.1 (K), D6.1 (K), J1.2, J2.2, J3.2, J4.2, J5.2, J6.2, R9.2, XT60IN1.2, XT60OUT1.2

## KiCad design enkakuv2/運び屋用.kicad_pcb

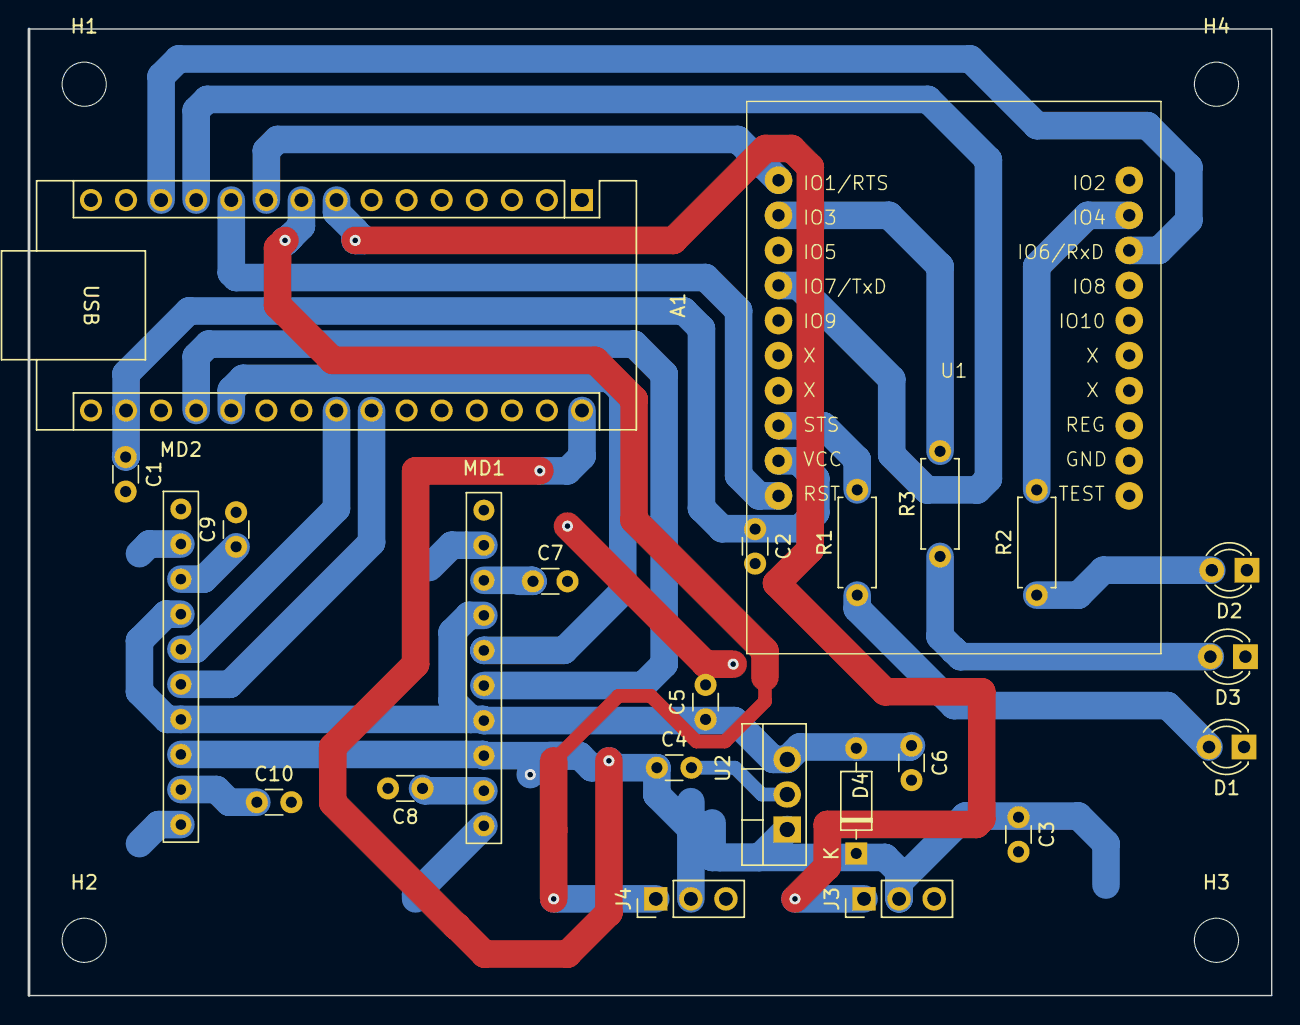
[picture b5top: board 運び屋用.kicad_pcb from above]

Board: 2 copper layers, 90.0 x 70.0 mm, 28 parts (0 on the bottom side), 24 nets.

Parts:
A1: Arduino_Nano_Every; Arduino_Nano
C1, C4, C5: 10μ; C_Disc_D3.0mm_W1.6mm_P2.50mm
C2, C3, C6: 0.1μ; C_Disc_D3.0mm_W1.6mm_P2.50mm
C7, C8, C9, C10: C; C_Disc_D3.0mm_W1.6mm_P2.50mm
D1, D2, D3: LED; LED_D3.0mm
D4: D; D_DO-35_SOD27_P7.62mm_Horizontal
H1, H2, H3, H4: MountingHole; MountingHole_3.2mm_M3
J3, J4: Conn_01x03; PinHeader_1x03_P2.54mm_Vertical
MD1, MD2: BA6222
R1, R2, R3: R; R_Axial_DIN0207_L6.3mm_D2.5mm_P7.62mm_Horizontal
U1: IM920sL; IM920c-ADP_1
U2: LM7805_TO220; TO-220-3_Vertical

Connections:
+3.3V: A1.17 (3V3), C1.1, C2.1, U1.17 (VCC)
+5V: C5.1, C6.1, D4.2 (A), MD1.4 (VR), MD1.7 (VCC1), MD2.4 (VR), MD2.7 (VCC1), U2.3 (VO)
+BATT: A1.30 (VIN), C3.1, C4.1, D4.1 (K), J3.2, J4.2, MD1.8 (VCC2), MD2.8 (VCC2), U2.1 (VI)
BUSY: A1.10 (D7), U1.1 (IO1/RTS/BUSY)
GND: A1.4 (GND), A1.29 (GND), C1.2, C2.2, C3.2, C4.2, C5.2, C6.2, C7.2, C8.2, C9.2, C10.2, D1.1 (K), D2.1 (K), D3.1 (K), J3.3, J4.3, MD1.1 (GND), MD2.1 (GND), U1.18 (GND), U2.2 (GND)
M1IN1: A1.20 (A1), MD1.5 (IN1)
M1IN2: A1.19 (A0), MD1.6 (IN2)
M2IN1: A1.23 (SDA/A4), MD2.5 (IN1)
M2IN2: A1.24 (SCL/A5), MD2.6 (IN2)
unnamed: D1.2 (A), R1.1
unnamed: D2.2 (A), R2.1
unnamed: D3.2 (A), R3.1
unnamed: C7.1, MD1.3 (CD1)
unnamed: C8.1, MD1.9 (CD2)
unnamed: C9.1, MD2.3 (CD1)
unnamed: C10.1, MD2.9 (CD2)
RESET: A1.11 (D8), U1.19 (RESET)
RX920: A1.13 (D10), U1.6 (IO6/RxD)
SERVO1: A1.8 (D5), J3.1
SERVO2: A1.9 (D6), J4.1
SLEEP: R2.2, U1.4 (IO4)
STATUS: R1.2, U1.15 (STATUS)
TX920: A1.12 (D9), U1.7 (IO7/TxD)
XMIT: R3.2, U1.3 (IO3)
